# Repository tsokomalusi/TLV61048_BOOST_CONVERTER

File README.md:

# TLV61048_BOOST_CONVERTER

## Introduction
Using The Engineering Experience's YouTube channel [The Engineering Experience](https://www.youtube.com/@TheEngineeringExperienceYT) as a guide, 
I completed my first PCB design practice project for a boost converter.

## Schematic Capture

## PCB Layout (2-Layer Design)
### All layers with filled zones

## 3D Overview
### Top View

### Bottom View

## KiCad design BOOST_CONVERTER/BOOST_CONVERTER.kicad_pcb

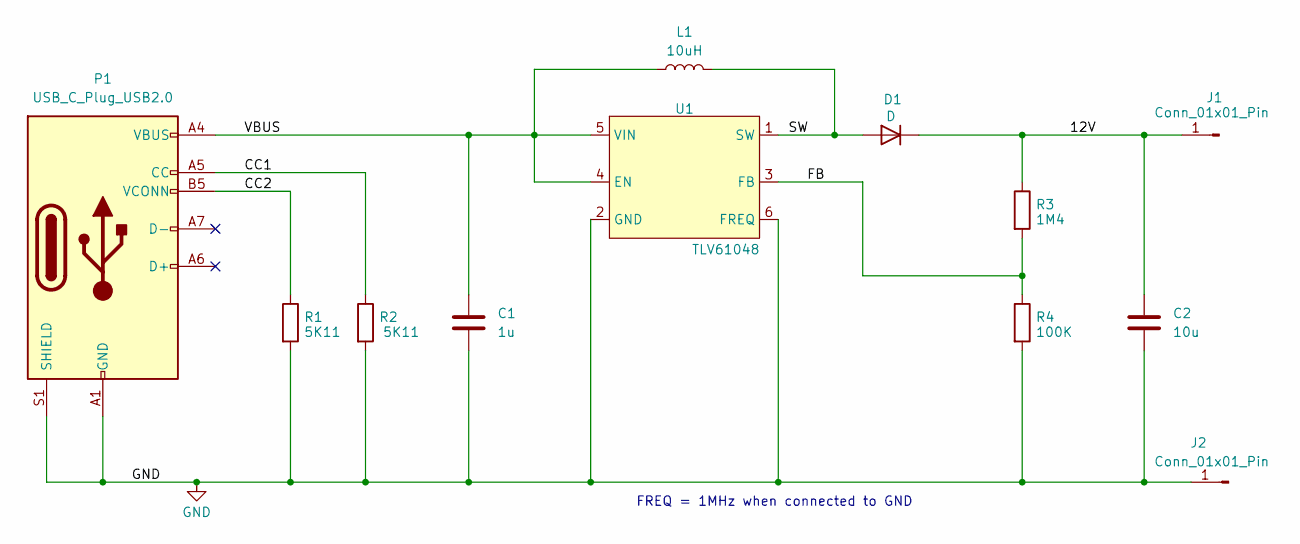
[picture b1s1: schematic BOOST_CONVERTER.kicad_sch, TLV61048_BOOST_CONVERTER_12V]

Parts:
C1: 1u; C_1206_3216Metric
C2: 10u; C_1206_3216Metric
D1: D; D_SOD-123
J1, J2: Conn_01x01_Pin; PinHeader_1x01_P2.54mm_Vertical
L1: 10uH; L_Bourns-SRN8040_8x8.15mm
P1: USB_C_Plug_USB2.0; USB_C_Receptacle_GCT_USB4105-xx-A_16P_TopMnt_Horizontal
R1, R2: 5K11; R_0402_1005Metric
R3: 1M4; R_0603_1608Metric
R4: 100K; R_0603_1608Metric
U1: TLV61048; SOT-23-6

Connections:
/12V: C2.1, D1.1 (K), J1.1, R3.1
/CC1: P1.A5 (CC), R2.1
/CC2: P1.B5 (VCONN), R1.1
/FB: R3.2, R4.1, U1.3 (FB)
/SW: D1.2 (A), L1.2, U1.1 (SW)
/VBUS: C1.1, L1.1, P1.A4 (VBUS), P1.A9 (VBUS), P1.B4 (VBUS), P1.B9 (VBUS), U1.4 (EN), U1.5 (VIN)
GND: C1.2, C2.2, J2.1, P1.A1 (GND), P1.A12 (GND), P1.B1 (GND), P1.B12 (GND), P1.S1 (SHIELD), R1.2, R2.2, R4.2, U1.2 (GND), U1.6 (FREQ)

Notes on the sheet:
FREQ = 1MHz when connected to GND

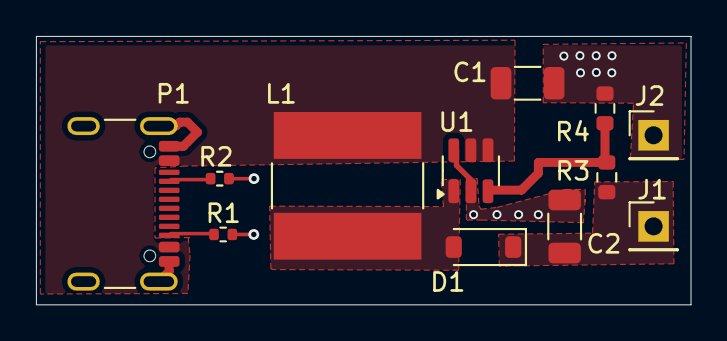
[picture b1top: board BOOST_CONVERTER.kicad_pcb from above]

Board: 2 copper layers, 36.4 x 14.9 mm, 12 parts (0 on the bottom side), 7 nets.
